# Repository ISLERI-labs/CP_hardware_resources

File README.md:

**Project Status:** Active Testing

**Author/developed by:** Omm Prakash Das

**Latest Stable Hardware:** CEREPHYTE 5

**Current Prototype:** CEREPHYTE 5 (Prototype testing)

**Validation Status:** Hardware validation pending

**License:** CHL v1.0

# CEREPHYTE

License: CHL v1.0

This project is source-available.

✔ Personal Use
✔ Education
✔ Research
✔ Modification
✔ Redistribution

✘ Commercial Manufacturing
✘ Commercial Sale
✘ Commercial Distribution

See LICENSE for details.

## Project Repositories

- [CP_hardware_resources](https://github.com/ISLERI-labs/CP_hardware_resources) — hardware designs and resources (this repository).
- [CP_software](https://github.com/ISLERI-labs/CP_software) — project software.
- [CP_firmware](https://github.com/ISLERI-labs/CP_firmware) — project firmware.

## Documentation

- See [CHANGELOG.md](CHANGELOG.md) for release notes and project updates.
- See [THIRD_PARTY.md](LICENSE/THIRD_PARTY.md) for third-party licensing and attribution details.

> ## Development Status
>
> **CEREPHYTE is currently under active development.**
>
> The hardware designs, schematics, and documentation in this repository are **experimental** and are being released to encourage transparency, learning, community feedback, and collaborative research.
>
> At this stage, the project **should not be considered production-ready** or suitable for safety-critical or commercial applications.
>
> Bug reports, design reviews, and constructive feedback are welcome.

## Copyright and Licensing

Copyright © 2026 Omm Prakash Das.

The CEREPHYTE hardware designs and associated materials are provided under the licenses specified in this repository. Hardware design files are governed by the CerePhyte Hardware License (CHL) v1.0. Documentation and other materials are licensed under CC BY-SA 4.0 where expressly indicated.

See "LICENSE" (LICENSE) and the relevant file-level notices for the applicable terms. Third-party materials remain subject to their respective licenses.

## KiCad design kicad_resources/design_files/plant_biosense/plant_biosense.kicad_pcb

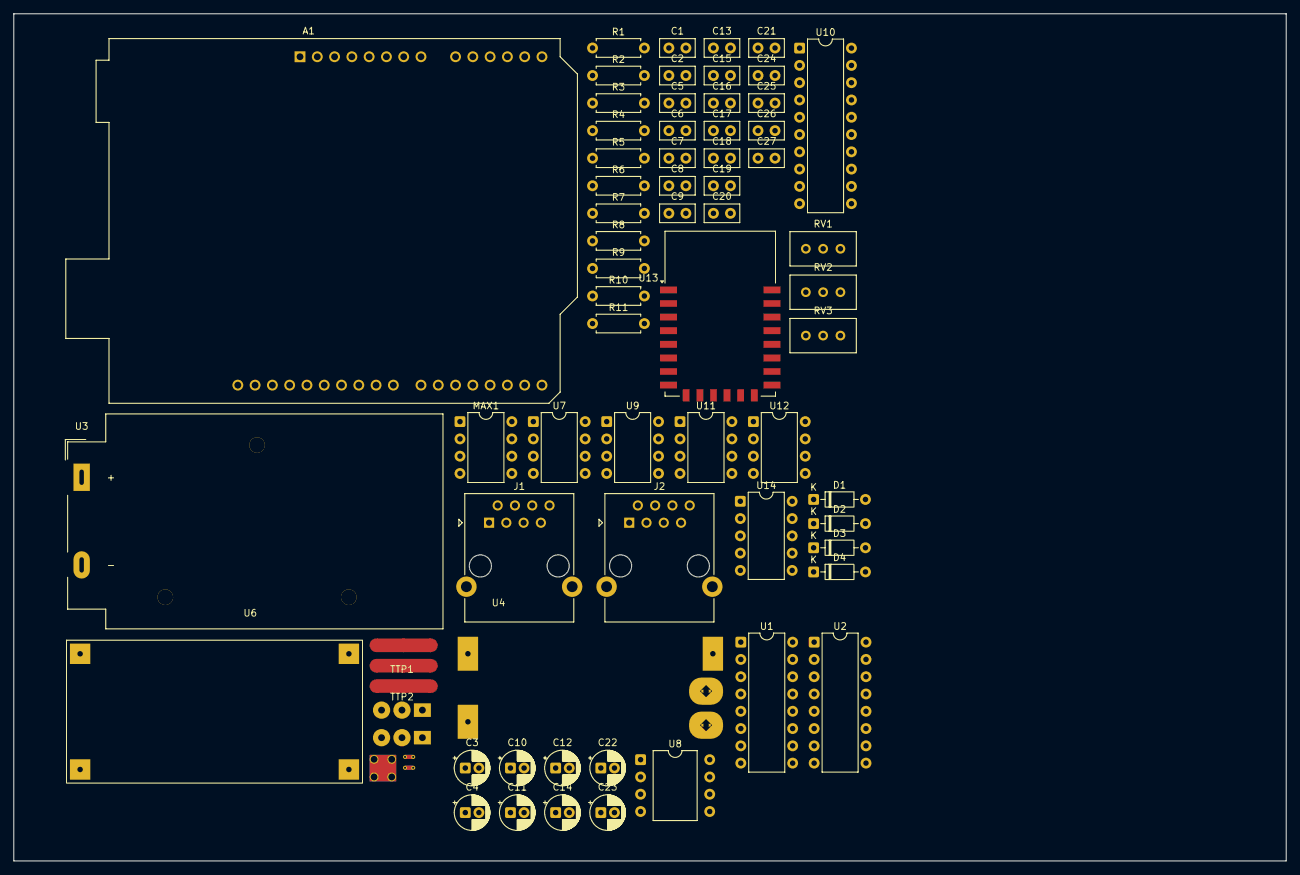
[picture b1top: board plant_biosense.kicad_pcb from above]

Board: 2 copper layers, 187.0 x 124.5 mm, 70 parts (0 on the bottom side), 71 nets, no tracks yet.

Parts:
A1: Arduino_UNO_R3
C1, C2, C5, C6, C7, C8, C15, C16, C17, C20, C21, C24, C25, C26, C27: 0.1uf; C_Disc_D5.0mm_W2.5mm_P2.50mm
C3, C4, C10, C12, C22, C23: 10uf; CP_Radial_D5.0mm_P2.00mm
C9, C13, C18, C19: 1uf; C_Disc_D5.0mm_W2.5mm_P2.50mm
C11: 100uf; CP_Radial_D5.0mm_P2.00mm
C14: 0.47uf; CP_Radial_D5.0mm_P2.00mm
D1, D2, D3, D4: BAT85; D_DO-35_SOD27_P7.62mm_Horizontal
J1, J2: RJ45_Shielded; RJ45_Ninigi_GE
MAX1: DIP-8_W7.62mm
NT1, NT2: NetTie_2; NetTie-2_THT_Pad0.3mm
NT3: NetTie_3_Tee; NetTie-3_SMD_Pad2.0mm
NT4, NT5: NetTie_3; NetTie-3_SMD_Pad2.0mm
NT6: NetTie_4; NetTie-4_THT_Pad1.0mm
R1, R2, R4, R5, R6, R10: 1M; R_Axial_DIN0207_L6.3mm_D2.5mm_P7.62mm_Horizontal
R3: 10E; R_Axial_DIN0207_L6.3mm_D2.5mm_P7.62mm_Horizontal
R7, R9: 10k; R_Axial_DIN0207_L6.3mm_D2.5mm_P7.62mm_Horizontal
R8, R11: 1k; R_Axial_DIN0207_L6.3mm_D2.5mm_P7.62mm_Horizontal
RV1, RV2, RV3: 10k; Potentiometer_Bourns_3296W_Vertical
TTP1, TTP2: TTP223_module
U1, U2: CD4051B; DIP-16_W7.62mm
U3: 2S4P LI-ION BATTERY; BatteryHolder_MPD_BA9VPC_1xPP3
U4: 2S LI-ION BMS 10A; 2s LI-ION BMS 10A
U6: XL4015; XL4015 5A DC-DC Step Down Adjustable Power Supply Buck Modu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
U7: AD620_instrumentation_amplifier_module; DIP-8_W7.62mm
U8: INA219AxD; DIP-8_W10.16mm
U9, U11: OP07; DIP-8_W7.62mm
U10: TXS0108EPW; DIP-20_W7.62mm
U12: TL081; DIP-8_W7.62mm
U13: NodeMCU1.0(ESP-12E); ESP-12E
U14: ADS1115IDGS; DIP-10_W7.62mm

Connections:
/Aout: R8.1, R11.2, U12.2 (-), U12.6
/BP+: U4.1 (p+), U6.1 (IN+), U8.7 (IN-), U8.8 (IN+)
/BP-: NT3.1, U4.2 (p-), U6.2 (IN-)
/EESPC_out1: C6.1, NT1.2, R1.1, U7.4 (+s)
/EESPC_out2: C7.1, NT2.2, R2.1, U7.3 (-s)
/HSCL: A1.14 (SCL/A5), U10.18 (B2)
/HSDA: A1.13 (SDA/A4), U10.20 (B1)
/INASCL: U8.4 (SCL), U10.12 (B8)
/INASDA: U8.3 (SDA), U10.13 (B7)
/INH1: A1.23 (D8), U1.6 (INH)
/INH2: A1.24 (D9), U2.6 (INH)
/IO1: TTP1.2 (I/O), U10.17 (B3)
/IO2: TTP2.2 (I/O), U10.16 (B4)
/LSCL: U10.3 (A2), U10.9 (A8)
/LSDA: U10.1 (A1), U10.8 (A7)
/SCL: A1.32 (SCL/A5), U14.10 (SCL)
/SDA: A1.31 (SDA/A4), U14.9 (SDA)
/a1: A1.17 (D2), U1.11 (A)
/a2: A1.20 (D5), U2.11 (A)
/arduino5v: A1.5 (+5V), C23.1, C24.1, MAX1.8 (vcc), U10.19 (VCCB), U14.8 (VDD)
/b1: A1.18 (D3), U1.10 (B)
/b2: A1.21 (D6), U2.10 (B)
/c1: A1.19 (D4), U1.9 (C)
/c2: A1.22 (D7), U2.9 (C)
/esp3.3v: U10.2 (VCCA), U10.10 (OE), U13.11 (3.3V)
/m0: J1.8, U1.13 (X0), U2.13 (X0)
/m1: J1.7, U1.14 (X1), U2.14 (X1)
/m2: J1.6, U1.15 (X2), U2.15 (X2)
/m3: J1.5, U1.12 (X3), U2.12 (X3)
/m4: J1.4, U1.1 (X4), U2.1 (X4)
/m5: J1.3, U1.5 (X5), U2.5 (X5)
/m6: J1.2, U1.2 (X6), U2.2 (X6)
/m7: J1.1, U1.4 (X7), U2.4 (X7)
/mux_out1: D1.2 (A), D2.1 (K), NT1.1, U1.3 (X)
/mux_out2: D3.2 (A), D4.1 (K), NT2.1, U2.3 (X)
/vdd: A1.8 (VIN), C1.1, C2.1, C3.1, C4.1, C8.1, C10.1, C12.1, C14.1, C17.1, C22.1, C25.1, D1.1 (K), D3.1 (K), J2.7, NT6.2, TTP1.1 (VCC), TTP2.1 (VCC), U1.16 (VDD), U2.16 (VDD), U6.3 (OUT+), U8.5 (VS), U13.15 (VIN)
/vee: C11.2, C16.1, C21.1, C27.1, D2.2 (A), D4.2 (A), R3.2, RV1.2, RV2.2, RV3.2, U1.7 (VEE), U2.7 (VEE), U9.4 (V-), U11.4 (V-), U12.4 (V-)
GND: C10.2, C11.1, C14.2, NT3.3, NT4.2
GNDA: C1.2, C2.2, C3.2, C4.2, C5.2, C6.2, C7.2, C15.1, C16.2, C18.1, C19.1, C20.2, C21.2, C26.2, C27.2, J1.SH, NT4.1, R1.2, R2.2, R4.2, R5.1, R6.2, R10.1, U1.8 (VSS), U2.8 (VSS), U7.2 (GND), U7.6 (GND), U7.8 (GND)
GNDD: A1.6 (GND), C12.2, C17.2, C22.2, C23.2, C24.2, C25.2, J2.5, J2.8, J2.SH, MAX1.5 (GND), NT4.3, TTP1.3 (GND), TTP2.3 (GND), U8.1 (A1), U8.2 (A0), U8.6 (GND), U10.11 (GND), U13.14 (GND), U14.3 (GND)
unnamed: A1.9 (A0), R8.2
unnamed: A1.15 (D0/RX), MAX1.1 (RO)
unnamed: A1.16 (D1/TX), MAX1.4 (DI)
unnamed: A1.25 (D10), MAX1.2 (RE), MAX1.3 (DE)
unnamed: A1.26 (D11), J2.6
unnamed: A1.27 (D12), J2.4
unnamed: A1.28 (D13), J2.3
unnamed: C9.2, C13.1, R4.1
unnamed: C18.2, R7.2, R9.1
unnamed: J2.1, MAX1.6 (A)
unnamed: J2.2, MAX1.7 (B)
unnamed: NT5.2, NT6.3
unnamed: RV1.1, U9.1 (VOS)
unnamed: RV1.3, U9.8 (VOS)
unnamed: RV2.1, U11.1 (VOS)
unnamed: RV2.3, U11.8 (VOS)
unnamed: RV3.1, U12.1 (NULL)
unnamed: RV3.3, U12.5 (NULL)
unnamed: U3.2 (CB-), U4.5 (B-)
unnamed: C8.2, NT3.2, U6.4 (OUT-)
unnamed: R3.1, U7.5 (-v_out)
unnamed: C9.1, U7.7 (Vout)
unnamed: C5.1, NT5.1, U7.1 (vin)
unnamed: C13.2, R5.2, R6.1, U9.3 (+)
unnamed: R7.1, U9.2 (-), U9.6
unnamed: C15.2, NT5.3, U9.7 (V+)
unnamed: C19.2, R9.2, R10.2, U11.3 (+)
unnamed: U11.2 (-), U11.6, U12.3 (+)
unnamed: C20.1, NT6.1, U11.7 (V+)
unnamed: C26.1, NT6.4, U12.7 (V+)
unnamed: R11.1, U14.4 (AIN0)

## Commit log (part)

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2026-06-28 initial commits
